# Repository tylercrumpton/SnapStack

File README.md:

# SnapStack
Stackable modular board ecosystem for SNAP wireless microcontrollers.

## Ideas
 * The boards while use two rows of extra-tall headers to all the modules to stack.
 * All or most of the modules need to be compatible with each other
 * Should be breadboard-able
 * Try to keep each module cost <$10
 * Reuse PCBs with no-pop parts as much as possible (at least for early runs)
 * Modules that use i2c devices can be autodetected
 
## Interface
 * Two rows of 16-pin tall stackable pin headers for a total of 32 interface pins
  * 24 of the pins will breakout the SNAP module's pins
    * 19 GPIO
      * 4 UART (UART0 RX/TX, UART1 RX/TX)
      * 3 Analog in
      * 3 CBUS/SPI (CLK, CDATA/MOSI, RDATA/MISO)
      * 6 Digital interrupts 
      * 2 i2c (SCL, SDA)
      * 1 PWM
    * 2 GND
    * 1 3v3
    * 1 Reset
    * 1 Misc (GPIO on RF200, PTGO on RF100)
  * At least one pin will be reserved for a possible 5V power source
  * The other seven will be reserved for future use

## Pinout
     1 GND   (SNAP module ground input)
     2 PWM   (Digital IO pin with PWM)
     3 D0    (Digital IO pin w/ interrupt)
     4 D1    (Digital IO pin w/ interrupt)
     5 RX0   (UART0 RX on SNAP module)
     6 TX0   (UART0 TX on SNAP module)
     7 D2    (Digital IO pin w/ interrupt)
     8 D3    (Digital IO pin w/ interrupt)
     9 RX1   (UART1 RX on SNAP module)
    10 TX1   (UART1 TX on SNAP module)
    11 D4    (Digital IO pin w/ interrupt)
    12 D5    (Digital IO pin w/ interrupt)
    13 5v    (5V power source provided from 5V module)
    14 RES0  (Reserved for future use)
    15 RES1  (Reserved for future use)
    16 RES2  (Reserved for future use)
    17 RES3  (Reserved for future use)
    18 RES4  (Reserved for future use)
    19 RES5  (Reserved for future use)
    20 RES6  (Reserved for future use)
    21 A0    (Analog/Digital IO pin)
    22 MOSI  (SPI MOSI output)
    23 CLK   (SPI clock output)
    24 MISO  (SPI MISO input)
    25 A1    (Analog/Digital IO pin)
    26 A2    (Analog/Digital IO pin)
    27 SDA   (I2C data line)
    28 SCL   (I2C clock line)
    29 3v3   (SNAP module 3.3V power input)
    30 PTGO  (Debug pin on RF100, GPIO on RF200)
    31 RESET (SNAP module reset)
    32 GND   (SNAP module ground input)

## Modules

### Completed Modules

### Modules in Progress
 * Coin Cell Battery
 * SNAP Module Socket

### Module Ideas
 * Temperature Sensor
 * Humidity Sensor
 * Flash Memory Board
 * Buzzer
 * Accelerometer
 * Coin Cell Battery
 * Rechargeable LiPo Battery
 * USB Plug
 * Bluetooth
 * WiFi
 * Real-time Clock
 * Button
 * RGB LED
 * Light Sensor
 * Microphone
 * 5V Power Board

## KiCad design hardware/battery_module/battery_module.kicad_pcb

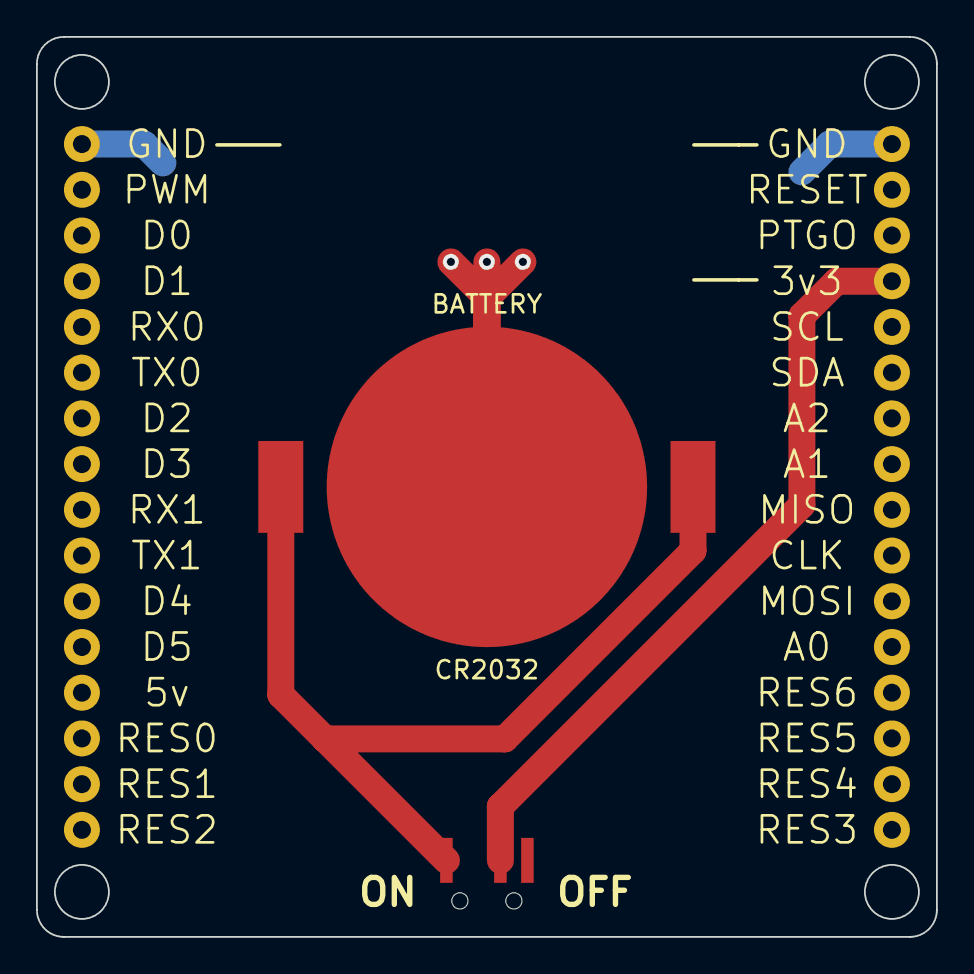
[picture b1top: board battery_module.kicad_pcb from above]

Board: 2 copper layers, 50.0 x 50.0 mm, 3 parts (0 on the bottom side), 3 nets.

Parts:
CR2032: BATTERY; CR2032_HOLDER
SW1: SPST; SPDT_slide_switch
U1: SnapStack

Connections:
unnamed: CR2032.1, SW1.1
unnamed: CR2032.2, U1.1, U1.32
unnamed: SW1.2, U1.29

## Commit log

2015-01-23 Updated README with some ideas.
2015-01-24 Updated README with module and interface plans.
2015-01-25 Added more specific pin descriptions to README.
2015-01-25 Fixed formatting in README.
2015-01-26 Added .gitignore file for hardware directory.
2015-01-26 Created SnapStack module template board.
2015-01-27 Added screenshot of module template to README.
2015-01-28 Added pinout to README.
2015-01-30 Added schematic for battery board.
2015-01-31 Fixed screenshot of pinout in README.
2015-01-31 Placed all parts and added edge routes from template.
2015-02-02 Finished battery board layout.
